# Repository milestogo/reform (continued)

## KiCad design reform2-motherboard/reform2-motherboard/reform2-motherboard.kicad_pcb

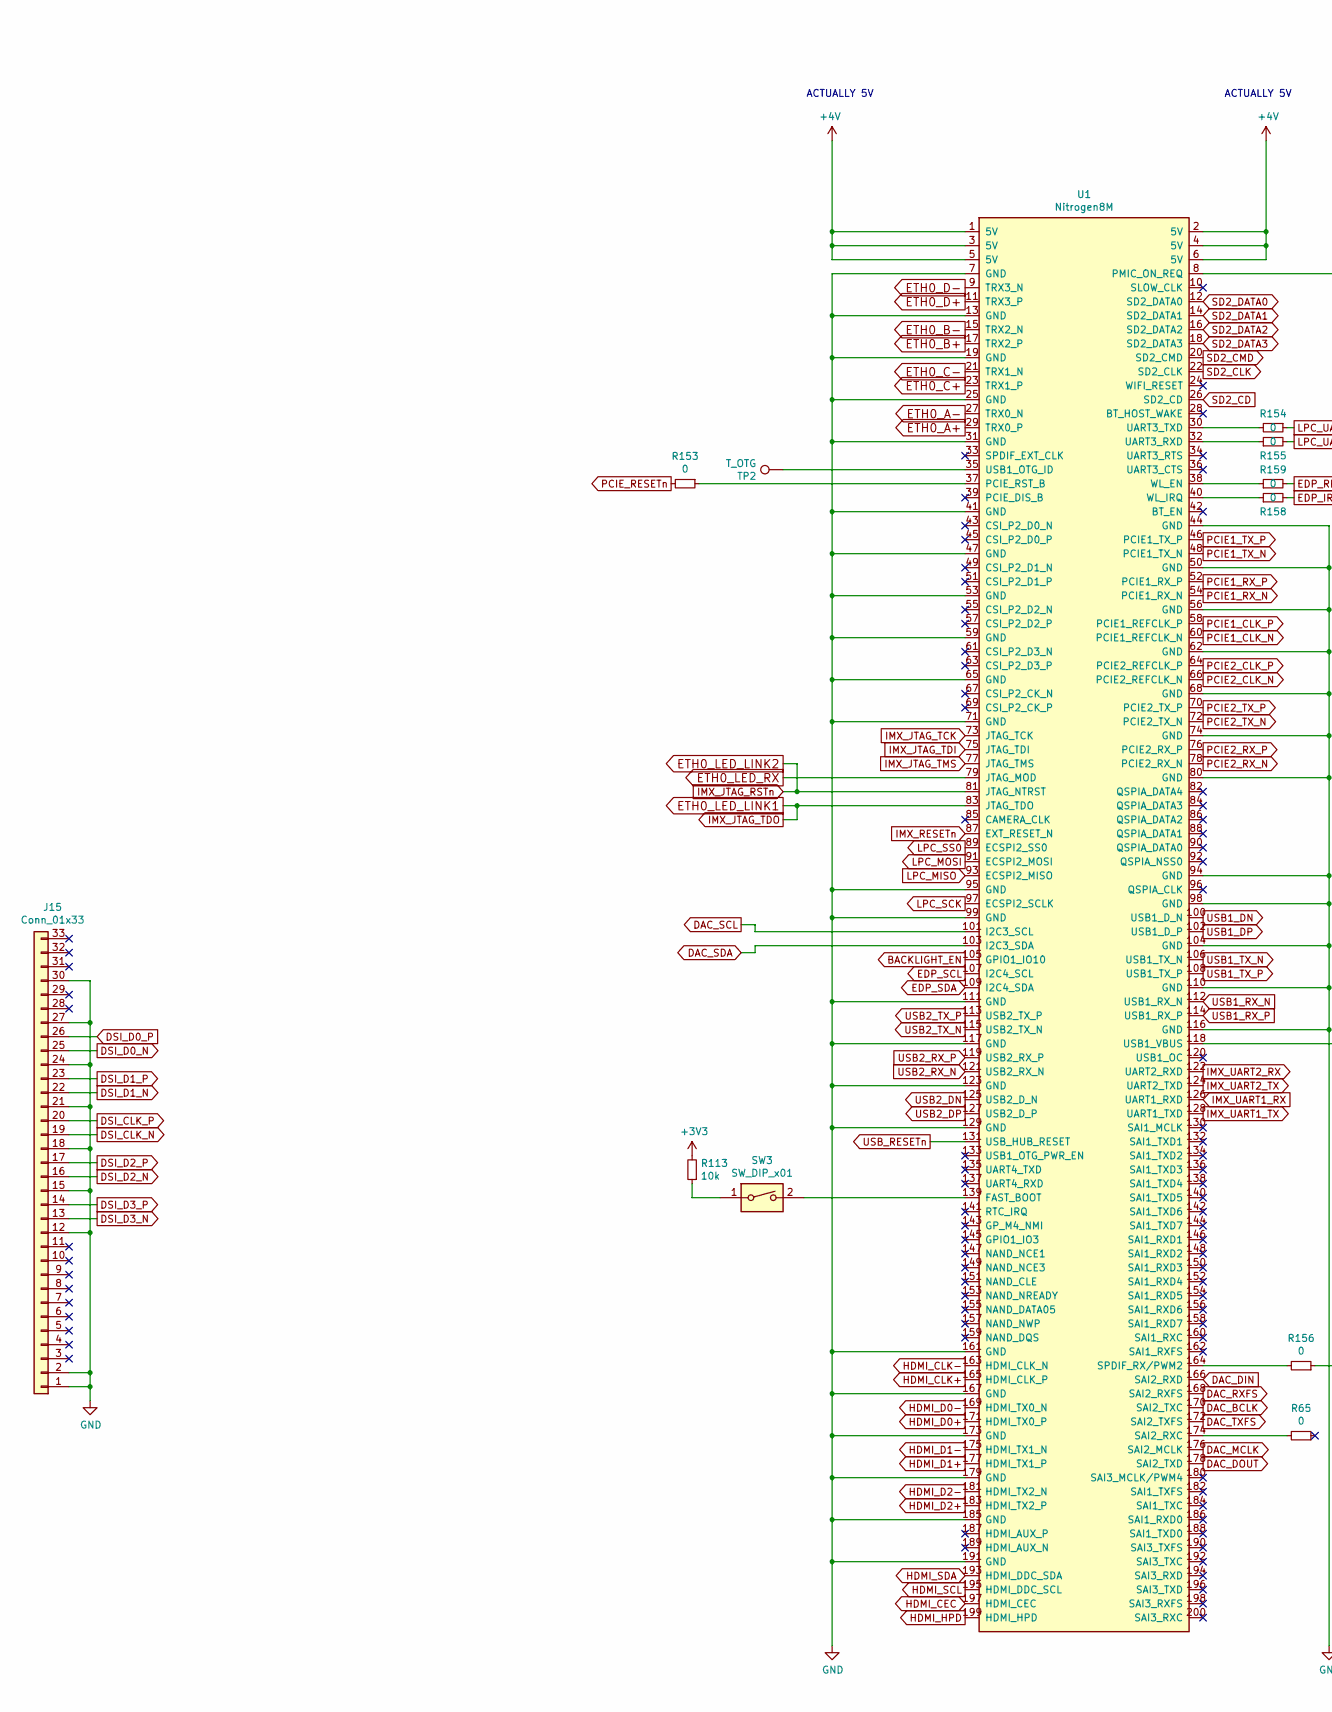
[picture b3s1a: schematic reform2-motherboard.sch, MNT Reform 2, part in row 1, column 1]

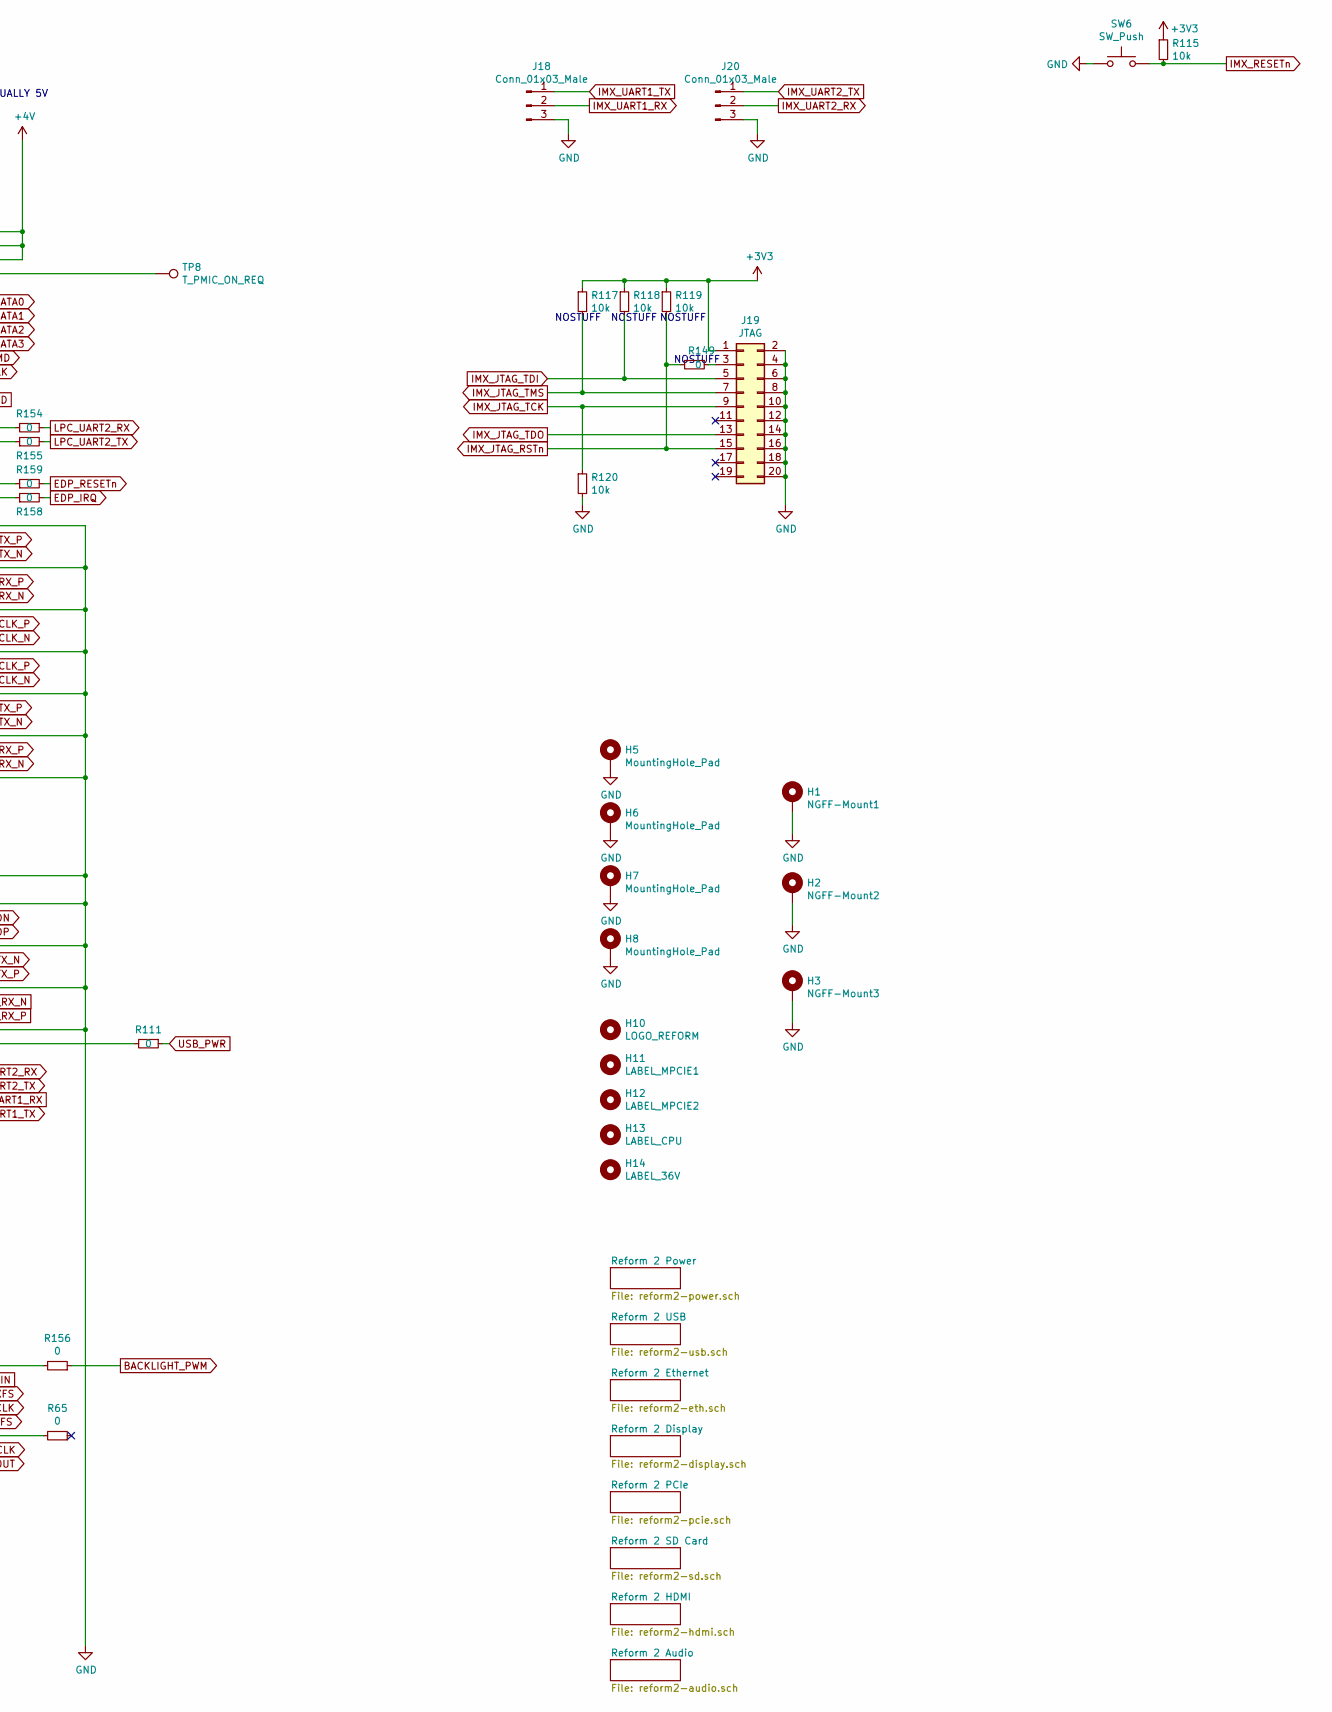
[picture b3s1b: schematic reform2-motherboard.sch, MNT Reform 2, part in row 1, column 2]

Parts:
H1: NGFF-Mount1; MountingHole_3.2mm_M3_DIN965_Pad
H2: NGFF-Mount2; MountingHole_3.2mm_M3_DIN965_Pad
H3: NGFF-Mount3; MountingHole_3.2mm_M3_DIN965_Pad
H5, H6, H7, H8: MountingHole_Pad; MountingHole_2.2mm_M2_DIN965_Pad
H10: LOGO_REFORM; mntreform
H11: LABEL_MPCIE1; mpcie
H12: LABEL_MPCIE2; nvme
H13: LABEL_CPU; cpu
H14: LABEL_36V; 36v
J15: Conn_01x33; Hirose_FH12-33S-0.5SH_1x33-1MP_P0.50mm_Horizontal
J18, J20: Conn_01x03_Male; PinHeader_1x03_P2.54mm_Vertical
J19: JTAG; PinHeader_2x10_P2.54mm_Vertical
R65, R111, R149, R153, R154, R155, R156, R158, R159: 0; R_0603_1608Metric
R113, R115, R117, R118, R119, R120: 10k; R_0603_1608Metric
SW3: SW_DIP_x01; SW_DIP_SPSTx01_Slide_Omron_A6S-110x_W8.9mm_P2.54mm
SW6: SW_Push; SW_Push_1P1T_NO_CK_KMR2
TP2: T_OTG; TestPoint_Pad_D1.0mm
TP8: T_PMIC_ON_REQ; TestPoint_Pad_D1.0mm
U1: Nitrogen8M; TE_1473149-4

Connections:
+4V: U1.1 (5V), U1.2 (5V), U1.3 (5V), U1.4 (5V), U1.5 (5V), U1.6 (5V); also elsewhere on the board
BACKLIGHT_EN: U1.105 (GPIO1_IO10); also elsewhere on the board
BACKLIGHT_PWM: R156.1; also elsewhere on the board
DAC_BCLK: U1.170 (SAI2_TXC); also elsewhere on the board
DAC_DIN: U1.166 (SAI2_RXD); also elsewhere on the board
DAC_DOUT: U1.178 (SAI2_TXD); also elsewhere on the board
DAC_MCLK: U1.176 (SAI2_MCLK); also elsewhere on the board
DAC_RXFS: U1.168 (SAI2_RXFS); also elsewhere on the board
DAC_SCL: U1.101 (I2C3_SCL); also elsewhere on the board
DAC_SDA: U1.103 (I2C3_SDA); also elsewhere on the board
DAC_TXFS: U1.172 (SAI2_TXFS); also elsewhere on the board
DSI_CLK_N: J15.19; also elsewhere on the board
DSI_CLK_P: J15.20; also elsewhere on the board
DSI_D0_N: J15.25; also elsewhere on the board
DSI_D0_P: J15.26; also elsewhere on the board
DSI_D1_N: J15.22; also elsewhere on the board
DSI_D1_P: J15.23; also elsewhere on the board
DSI_D2_N: J15.16; also elsewhere on the board
DSI_D2_P: J15.17; also elsewhere on the board
DSI_D3_N: J15.13; also elsewhere on the board
DSI_D3_P: J15.14; also elsewhere on the board
EDP_IRQ: R158.2; also elsewhere on the board
EDP_RESETn: R159.2; also elsewhere on the board
EDP_SCL: U1.107 (I2C4_SCL); also elsewhere on the board
EDP_SDA: U1.109 (I2C4_SDA); also elsewhere on the board
ETH0_A+: U1.29 (TRX0_P); also elsewhere on the board
ETH0_A-: U1.27 (TRX0_N); also elsewhere on the board
ETH0_B+: U1.17 (TRX2_P); also elsewhere on the board
ETH0_B-: U1.15 (TRX2_N); also elsewhere on the board
ETH0_C+: U1.23 (TRX1_P); also elsewhere on the board
ETH0_C-: U1.21 (TRX1_N); also elsewhere on the board
ETH0_D+: U1.11 (TRX3_P); also elsewhere on the board
ETH0_D-: U1.9 (TRX3_N); also elsewhere on the board
ETH0_LED_LINK1: J19.13, U1.83 (JTAG_TDO); also elsewhere on the board
ETH0_LED_LINK2: J19.15, R119.2, R149.2, U1.81 (JTAG_NTRST); also elsewhere on the board
ETH0_LED_RX: U1.79 (JTAG_MOD); also elsewhere on the board
GND: H1.1, H2.1, H3.1, H5.1, H6.1, H7.1, H8.1, J15.1, J15.2, J15.12, J15.15, J15.18, J15.21, J15.24, J15.27, J15.30, J18.3, J19.2, J19.4, J19.6, J19.8, J19.10, J19.12, J19.14, J19.16, J19.18, J19.20, J20.3, R120.2, SW6.1, U1.7 (GND), U1.13 (GND), U1.19 (GND), U1.25 (GND), U1.31 (GND), U1.41 (GND), U1.44 (GND), U1.47 (GND), U1.50 (GND), U1.53 (GND), U1.56 (GND), U1.59 (GND), U1.62 (GND), U1.65 (GND), U1.68 (GND), U1.71 (GND), U1.74 (GND), U1.80 (GND), U1.94 (GND), U1.95 (GND), U1.98 (GND), U1.99 (GND), U1.104 (GND), U1.110 (GND), U1.111 (GND), U1.116 (GND), U1.117 (GND), U1.123 (GND), U1.129 (GND), U1.161 (GND), U1.167 (GND), U1.173 (GND), U1.179 (GND), U1.185 (GND), U1.191 (GND); also elsewhere on the board
HDMI_CEC: U1.197 (HDMI_CEC); also elsewhere on the board
HDMI_CLK+: U1.165 (HDMI_CLK_P); also elsewhere on the board
HDMI_CLK-: U1.163 (HDMI_CLK_N); also elsewhere on the board
HDMI_D0+: U1.171 (HDMI_TX0_P); also elsewhere on the board
HDMI_D0-: U1.169 (HDMI_TX0_N); also elsewhere on the board
HDMI_D1+: U1.177 (HDMI_TX1_P); also elsewhere on the board
HDMI_D1-: U1.175 (HDMI_TX1_N); also elsewhere on the board
HDMI_D2+: U1.183 (HDMI_TX2_P); also elsewhere on the board
HDMI_D2-: U1.181 (HDMI_TX2_N); also elsewhere on the board
HDMI_HPD: U1.199 (HDMI_HPD); also elsewhere on the board
HDMI_SCL: U1.195 (HDMI_DDC_SCL); also elsewhere on the board
HDMI_SDA: U1.193 (HDMI_DDC_SDA); also elsewhere on the board
IMX_JTAG_TCK: J19.9, R120.1, U1.73 (JTAG_TCK); also elsewhere on the board
IMX_JTAG_TDI: J19.5, R118.2, U1.75 (JTAG_TDI); also elsewhere on the board
IMX_JTAG_TMS: J19.7, R117.2, U1.77 (JTAG_TMS); also elsewhere on the board
IMX_RESETn: R115.2, SW6.2, U1.87 (EXT_RESET_N); also elsewhere on the board
IMX_UART1_RX: J18.2, U1.126 (UART1_RXD); also elsewhere on the board
IMX_UART1_TX: J18.1, U1.128 (UART1_TXD); also elsewhere on the board
IMX_UART2_RX: J20.2, U1.122 (UART2_RXD); also elsewhere on the board
IMX_UART2_TX: J20.1, U1.124 (UART2_TXD); also elsewhere on the board
LPC_MISO: U1.93 (ECSPI2_MISO); also elsewhere on the board
LPC_MOSI: U1.91 (ECSPI2_MOSI); also elsewhere on the board
LPC_SCK: U1.97 (ECSPI2_SCLK); also elsewhere on the board
LPC_SS0: U1.89 (ECSPI2_SS0); also elsewhere on the board
LPC_UART2_RX: R154.1; also elsewhere on the board
LPC_UART2_TX: R155.2; also elsewhere on the board
unnamed: J19.3, R149.1
unnamed 349: R65.2, U1.174 (SAI2_RXC); also elsewhere on the board
unnamed 368: R111.2, U1.118 (USB1_VBUS); also elsewhere on the board
unnamed: R113.1, SW3.1
unnamed 384: R153.1, U1.37 (PCIE_RST_B); also elsewhere on the board
unnamed 385: R154.2, U1.30 (UART3_TXD); also elsewhere on the board
unnamed 386: R155.1, U1.32 (UART3_RXD); also elsewhere on the board
unnamed 387: R156.2, U1.164 (SPDIF_RX/PWM2); also elsewhere on the board
unnamed 388: R158.1, U1.40 (WL_IRQ); also elsewhere on the board
unnamed 389: R159.1, U1.38 (WL_EN); also elsewhere on the board
unnamed 390: SW3.2, U1.139 (FAST_BOOT); also elsewhere on the board
unnamed 392: TP2.1, U1.35 (USB1_OTG_ID); also elsewhere on the board
unnamed 397: TP8.1, U1.8 (PMIC_ON_REQ); also elsewhere on the board
unnamed 399: U1.10 (SLOW_CLK); also elsewhere on the board
unnamed 400: U1.24 (WIFI_RESET); also elsewhere on the board
unnamed 401: U1.28 (BT_HOST_WAKE); also elsewhere on the board
unnamed 402: U1.33 (SPDIF_EXT_CLK); also elsewhere on the board
unnamed 403: U1.34 (UART3_RTS); also elsewhere on the board
unnamed 404: U1.36 (UART3_CTS); also elsewhere on the board
unnamed 405: U1.39 (PCIE_DIS_B); also elsewhere on the board
unnamed 406: U1.42 (BT_EN); also elsewhere on the board
unnamed 407: U1.43 (CSI_P2_D0_N); also elsewhere on the board
unnamed 408: U1.45 (CSI_P2_D0_P); also elsewhere on the board
unnamed 409: U1.49 (CSI_P2_D1_N); also elsewhere on the board
unnamed 410: U1.51 (CSI_P2_D1_P); also elsewhere on the board
unnamed 411: U1.55 (CSI_P2_D2_N); also elsewhere on the board
unnamed 412: U1.57 (CSI_P2_D2_P); also elsewhere on the board
unnamed 413: U1.61 (CSI_P2_D3_N); also elsewhere on the board
unnamed 414: U1.63 (CSI_P2_D3_P); also elsewhere on the board
unnamed 415: U1.67 (CSI_P2_CK_N); also elsewhere on the board
unnamed 416: U1.69 (CSI_P2_CK_P); also elsewhere on the board
unnamed 417: U1.82 (QSPIA_DATA4); also elsewhere on the board
unnamed 418: U1.84 (QSPIA_DATA3); also elsewhere on the board
unnamed 419: U1.85 (CAMERA_CLK); also elsewhere on the board
unnamed 420: U1.86 (QSPIA_DATA2); also elsewhere on the board
unnamed 421: U1.88 (QSPIA_DATA1); also elsewhere on the board
unnamed 422: U1.90 (QSPIA_DATA0); also elsewhere on the board
unnamed 423: U1.92 (QSPIA_NSS0); also elsewhere on the board
unnamed 424: U1.96 (QSPIA_CLK); also elsewhere on the board
unnamed 425: U1.120 (USB1_OC); also elsewhere on the board
unnamed 426: U1.130 (SAI1_MCLK); also elsewhere on the board
unnamed 427: U1.132 (SAI1_TXD1); also elsewhere on the board
unnamed 428: U1.133 (USB1_OTG_PWR_EN); also elsewhere on the board
unnamed 429: U1.134 (SAI1_TXD2); also elsewhere on the board
unnamed 430: U1.135 (UART4_TXD); also elsewhere on the board
unnamed 431: U1.136 (SAI1_TXD3); also elsewhere on the board
unnamed 432: U1.137 (UART4_RXD); also elsewhere on the board
unnamed 433: U1.138 (SAI1_TXD4); also elsewhere on the board
unnamed 434: U1.140 (SAI1_TXD5); also elsewhere on the board
unnamed 435: U1.141 (RTC_IRQ); also elsewhere on the board
unnamed 436: U1.142 (SAI1_TXD6); also elsewhere on the board
unnamed 437: U1.143 (GP_M4_NMI); also elsewhere on the board
unnamed 438: U1.144 (SAI1_TXD7); also elsewhere on the board
unnamed 439: U1.145 (GPIO1_IO3); also elsewhere on the board
unnamed 440: U1.146 (SAI1_RXD1); also elsewhere on the board
unnamed 441: U1.147 (NAND_NCE1); also elsewhere on the board
unnamed 442: U1.148 (SAI1_RXD2); also elsewhere on the board
unnamed 443: U1.149 (NAND_NCE3); also elsewhere on the board
unnamed 444: U1.150 (SAI1_RXD3); also elsewhere on the board
unnamed 445: U1.151 (NAND_CLE); also elsewhere on the board
unnamed 446: U1.152 (SAI1_RXD4); also elsewhere on the board
unnamed 447: U1.153 (NAND_NREADY); also elsewhere on the board
unnamed 448: U1.154 (SAI1_RXD5); also elsewhere on the board
unnamed 449: U1.155 (NAND_DATA05); also elsewhere on the board
unnamed 450: U1.156 (SAI1_RXD6); also elsewhere on the board
unnamed 451: U1.157 (NAND_NWP); also elsewhere on the board
unnamed 452: U1.158 (SAI1_RXD7); also elsewhere on the board
unnamed 453: U1.159 (NAND_DQS); also elsewhere on the board
unnamed 454: U1.160 (SAI1_RXC); also elsewhere on the board
unnamed 455: U1.162 (SAI1_RXFS); also elsewhere on the board
unnamed 456: U1.180 (SAI3_MCLK/PWM4); also elsewhere on the board
unnamed 457: U1.182 (SAI1_TXFS); also elsewhere on the board
unnamed 458: U1.184 (SAI1_TXC); also elsewhere on the board
unnamed 459: U1.186 (SAI1_RXD0); also elsewhere on the board
unnamed 460: U1.187 (HDMI_AUX_P); also elsewhere on the board
unnamed 461: U1.188 (SAI1_TXD0); also elsewhere on the board
unnamed 462: U1.189 (HDMI_AUX_N); also elsewhere on the board
unnamed 463: U1.190 (SAI3_TXFS); also elsewhere on the board
unnamed 464: U1.192 (SAI3_TXC); also elsewhere on the board
unnamed 465: U1.194 (SAI3_RXD); also elsewhere on the board
unnamed 466: U1.196 (SAI3_TXD); also elsewhere on the board
unnamed 467: U1.198 (SAI3_RXFS); also elsewhere on the board
unnamed 468: U1.200 (SAI3_RXC); also elsewhere on the board
PCIE1_CLK_N: U1.60 (PCIE1_REFCLK_N); also elsewhere on the board
PCIE1_CLK_P: U1.58 (PCIE1_REFCLK_P); also elsewhere on the board
PCIE1_RX_N: U1.54 (PCIE1_RX_N); also elsewhere on the board
PCIE1_RX_P: U1.52 (PCIE1_RX_P); also elsewhere on the board
PCIE1_TX_N: U1.48 (PCIE1_TX_N); also elsewhere on the board
PCIE1_TX_P: U1.46 (PCIE1_TX_P); also elsewhere on the board
PCIE2_CLK_N: U1.66 (PCIE2_REFCLK_N); also elsewhere on the board
PCIE2_CLK_P: U1.64 (PCIE2_REFCLK_P); also elsewhere on the board
PCIE2_RX_N: U1.78 (PCIE2_RX_N); also elsewhere on the board
PCIE2_RX_P: U1.76 (PCIE2_RX_P); also elsewhere on the board
PCIE2_TX_N: U1.72 (PCIE2_TX_N); also elsewhere on the board
PCIE2_TX_P: U1.70 (PCIE2_TX_P); also elsewhere on the board
PCIE_RESETn: R153.2; also elsewhere on the board
SD2_CD: U1.26 (SD2_CD); also elsewhere on the board
SD2_CLK: U1.22 (SD2_CLK); also elsewhere on the board
SD2_CMD: U1.20 (SD2_CMD); also elsewhere on the board
SD2_DATA0: U1.12 (SD2_DATA0); also elsewhere on the board
SD2_DATA1: U1.14 (SD2_DATA1); also elsewhere on the board
SD2_DATA2: U1.16 (SD2_DATA2); also elsewhere on the board
SD2_DATA3: U1.18 (SD2_DATA3); also elsewhere on the board
USB1_DN: U1.100 (USB1_D_N); also elsewhere on the board
USB1_DP: U1.102 (USB1_D_P); also elsewhere on the board
USB1_RX_N: U1.112 (USB1_RX_N); also elsewhere on the board
USB1_RX_P: U1.114 (USB1_RX_P); also elsewhere on the board
USB1_TX_N: U1.106 (USB1_TX_N); also elsewhere on the board
USB1_TX_P: U1.108 (USB1_TX_P); also elsewhere on the board
USB2_DN: U1.125 (USB2_D_N); also elsewhere on the board
USB2_DP: U1.127 (USB2_D_P); also elsewhere on the board
USB2_RX_N: U1.121 (USB2_RX_N); also elsewhere on the board
USB2_RX_P: U1.119 (USB2_RX_P); also elsewhere on the board
USB2_TX_N: U1.115 (USB2_TX_N); also elsewhere on the board
USB2_TX_P: U1.113 (USB2_TX_P); also elsewhere on the board
USB_PWR: R111.1; also elsewhere on the board
USB_RESETn: U1.131 (USB_HUB_RESET); also elsewhere on the board

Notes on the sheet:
ACTUALLY 5V
NOSTUFF

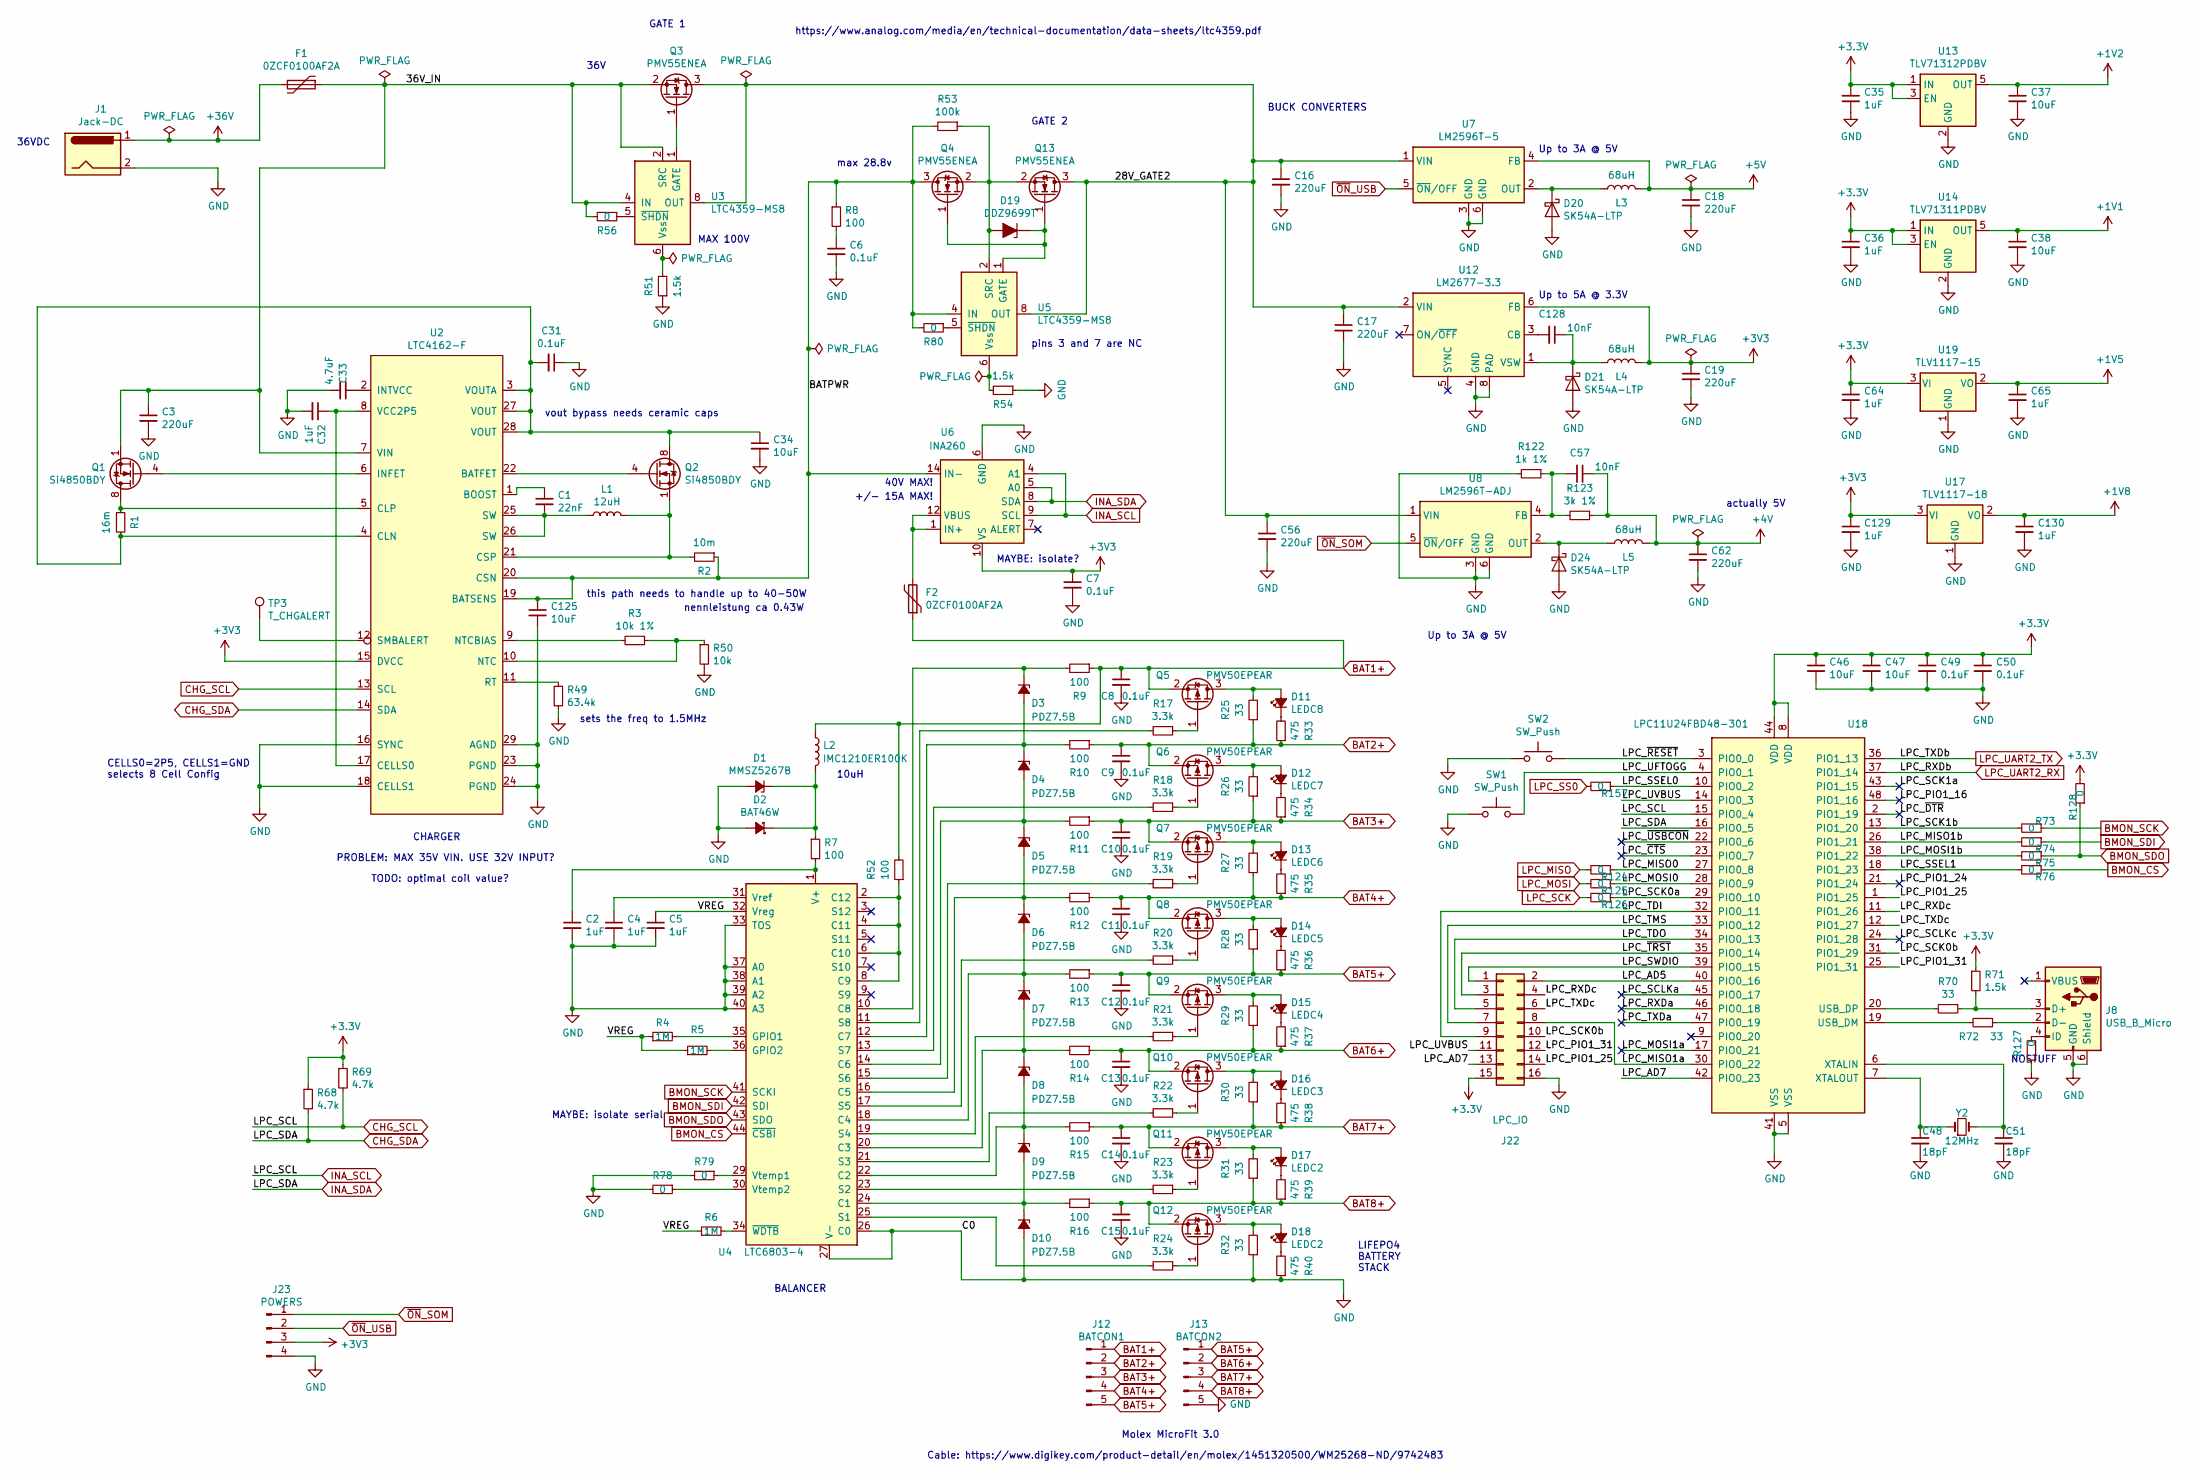
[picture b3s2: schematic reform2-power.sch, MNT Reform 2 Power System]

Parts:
C1: 22nF; C_0603_1608Metric
C2, C4, C5, C32, C35, C36, C64, C65, C129, C130: 1uF; C_0603_1608Metric
C3, C16, C17, C18, C19, C56, C62: 220uF; CP_Elec_8x10
C6, C7, C8, C9, C10, C11, C12, C13, C14, C15, C31, C49, C50: 0.1uF; C_0603_1608Metric
C33: 4.7uF; C_0603_1608Metric
C34, C37, C38, C46, C47, C125: 10uF; C_0603_1608Metric
C48, C51: 18pF; C_0603_1608Metric
C57, C128: 10nF; C_0603_1608Metric
D1: MMSZ5267B; D_SOD-123
D2: BAT46W; D_SOD-123
D3, D4, D5, D6, D7, D8, D9, D10: PDZ7.5B; D_SOD-323
D11: LEDC8; LED_0603_1608Metric
D12: LEDC7; LED_0603_1608Metric
D13: LEDC6; LED_0603_1608Metric
D14: LEDC5; LED_0603_1608Metric
D15: LEDC4; LED_0603_1608Metric
D16: LEDC3; LED_0603_1608Metric
D17, D18: LEDC2; LED_0603_1608Metric
D19: DDZ9699T; D_SOD-523
D20, D21, D24: SK54A-LTP; D_SMA
F1, F2: 0ZCF0100AF2A; Fuse_2920_7451Metric
J1: Jack-DC; SWC_RAPC712X
J8: USB_B_Micro; USB_Micro-B_Molex-105017-0001
J12: BATCON1; Molex_Micro-Fit_3.0_43650-0500_1x05_P3.00mm_Horizontal
J13: BATCON2; Molex_Micro-Fit_3.0_43650-0500_1x05_P3.00mm_Horizontal
J22: LPC_IO; PinHeader_2x08_P2.54mm_Vertical
J23: POWERS; PinHeader_1x04_P2.54mm_Vertical
L1: 12uH; L_Bourns_SRR1260
L2: IMC1210ER100K; L_1210_3225Metric
L3, L4, L5: 68uH; L_Bourns_SRR1210A
Q1, Q2: Si4850BDY; SOIC-8_3.9x4.9mm_P1.27mm
Q3, Q4, Q13: PMV55ENEA; SOT-23
Q5, Q6, Q7, Q8, Q9, Q10, Q11, Q12: PMV50EPEAR; SOT-23
R1: 16m; R_0612_1632Metric
R2: 10m; R_0612_1632Metric
R3: 10k 1%; R_0603_1608Metric
R4, R5, R6: 1M; R_0603_1608Metric
R7, R8, R9, R10, R11, R12, R13, R14, R15, R16, R52: 100; R_0603_1608Metric
R17, R18, R19, R20, R21, R22, R23, R24: 3.3k; R_0603_1608Metric
R25, R26, R27, R28, R29, R30, R31, R32, R70, R72: 33; R_0603_1608Metric
R33, R34, R35, R36, R37, R38, R39, R40: 475; R_0603_1608Metric
R49: 63.4k; R_0603_1608Metric
R50: 10k; R_0603_1608Metric
R51, R54, R71: 1.5k; R_0603_1608Metric
R53: 100k; R_0603_1608Metric
R56, R73, R74, R75, R76, R78, R79, R80, R124, R125, R126, R127, R128, R157: 0; R_0603_1608Metric
R68, R69: 4.7k; R_0603_1608Metric
R122: 1k 1%; R_0603_1608Metric
R123: 3k 1%; R_0603_1608Metric
SW1, SW2: SW_Push; SW_Push_1P1T_NO_CK_KMR2
TP3: T_CHGALERT; TestPoint_Pad_D1.0mm
U2: LTC4162-F; QFN-28-1EP_4x5mm_P0.5mm_EP2.65x3.65mm
U3, U5: LTC4359-MS8; MSOP-8_3x3mm_P0.65mm
U4: LTC6803-4; SSOP-44_5.3x12.8mm_P0.5mm
U6: INA260; TSSOP-16_4.4x5mm_P0.65mm
U7: LM2596T-5; TO-263-5_TabPin6
U8: LM2596T-ADJ; TO-263-5_TabPin6
U12: LM2677-3.3; TO-263-7_TabPin8
U13: TLV71312PDBV; SOT-23-5
U14: TLV71311PDBV; SOT-23-5
U17: TLV1117-18; SOT-223
U18: LPC11U24FBD48-301; LQFP-48_7x7mm_P0.5mm
U19: TLV1117-15; SOT-223
Y2: 12MHz; Crystal_SMD_Abracon_ABM8G-4Pin_3.2x2.5mm

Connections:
+1V1: C38.1, U14.5 (OUT); also elsewhere on the board
+1V2: C37.1, U13.5 (OUT); also elsewhere on the board
+1V5: C65.1, U19.2 (VO); also elsewhere on the board
+1V8: C130.1, U17.2 (VO); also elsewhere on the board
+4V: C57.1, C62.1, L5.2, R123.1; also elsewhere on the board
+36V: F1.2, J1.1
/Reform 2 Power/28V_GATE2: C16.1, C17.1, C56.1, Q3.3 (D), Q13.3 (D), U3.8 (OUT), U5.8 (OUT), U7.1 (VIN), U8.1 (VIN), U12.2 (VIN)
/Reform 2 Power/36V_IN: C3.1, F1.1, Q1.1 (S), Q1.2 (S), Q1.3 (S), Q3.2 (S), R56.2, U2.7 (VIN), U3.2 (SRC), U3.4 (IN)
/Reform 2 Power/BATPWR: C125.1, Q4.3 (D), R2.1, R8.1, R53.2, R80.2, U2.19 (BATSENS), U2.20 (CSN), U5.4 (IN), U6.14 (IN-), U6.15 (IN-), U6.16 (IN-)
/Reform 2 Power/LPC_AD5: J22.2, U18.40 (PIO0_16)
/Reform 2 Power/LPC_AD7: J22.13, U18.42 (PIO0_23)
/Reform 2 Power/LPC_MISO0: R124.1, U18.27 (PIO0_8)
/Reform 2 Power/LPC_MISO1a: J22.8, U18.30 (PIO0_22)
/Reform 2 Power/LPC_MISO1b: R74.2, U18.26 (PIO1_21)
/Reform 2 Power/LPC_MOSI0: R125.1, U18.28 (PIO0_9)
/Reform 2 Power/LPC_MOSI1a: U18.17 (PIO0_21)
/Reform 2 Power/LPC_MOSI1b: R75.2, U18.38 (PIO1_22)
/Reform 2 Power/LPC_PIO1_16: U18.48 (PIO1_16)
/Reform 2 Power/LPC_PIO1_24: U18.21 (PIO1_24)
/Reform 2 Power/LPC_PIO1_25: J22.14, U18.1 (PIO1_25)
/Reform 2 Power/LPC_PIO1_31: J22.12, U18.25 (PIO1_31)
/Reform 2 Power/LPC_RXDa: U18.46 (PIO0_18)
/Reform 2 Power/LPC_RXDc: J22.4, U18.11 (PIO1_26)
/Reform 2 Power/LPC_SCK0a: R126.1, U18.29 (PIO0_10)
/Reform 2 Power/LPC_SCK0b: J22.10, U18.31 (PIO1_29)
/Reform 2 Power/LPC_SCK1a: U18.43 (PIO1_15)
/Reform 2 Power/LPC_SCK1b: R73.2, U18.13 (PIO1_20)
/Reform 2 Power/LPC_SCLKa: U18.45 (PIO0_17)
/Reform 2 Power/LPC_SCLKc: U18.24 (PIO1_28)
/Reform 2 Power/LPC_SSEL0: R157.1, U18.10 (PIO0_2)
/Reform 2 Power/LPC_SSEL1: R76.2, U18.18 (PIO1_23)
/Reform 2 Power/LPC_SWDIO: J22.1, U18.39 (PIO0_15)
/Reform 2 Power/LPC_TDI: J22.9, U18.32 (PIO0_11)
/Reform 2 Power/LPC_TDO: J22.5, U18.34 (PIO0_13)
/Reform 2 Power/LPC_TMS: J22.7, U18.33 (PIO0_12)
/Reform 2 Power/LPC_TXDa: U18.47 (PIO0_19)
/Reform 2 Power/LPC_TXDc: J22.6, U18.12 (PIO1_27)
/Reform 2 Power/LPC_UFTOGG: SW1.2, U18.4 (PIO0_1)
/Reform 2 Power/LPC_UVBUS: J22.11, U18.14 (PIO0_3)
/Reform 2 Power/LPC_~CTS: U18.23 (PIO0_7)
/Reform 2 Power/LPC_~DTR: U18.2 (PIO1_19)
/Reform 2 Power/LPC_~RESET: SW2.2, U18.3 (PIO0_0)
/Reform 2 Power/LPC_~TRST: J22.3, U18.35 (PIO0_14)
/Reform 2 Power/LPC_~USBCON: U18.22 (PIO0_6)
/Reform 2 Power/VREG: C5.1, R4.1, R5.1, R6.1, U4.32 (Vreg)
BAT1+: C8.1, F2.1, J12.1, L2.1, Q5.2 (S), R9.1, R52.2
BAT2+: C9.1, J12.2, Q6.2 (S), R10.1, R25.1, R33.1
BAT3+: C10.1, J12.3, Q7.2 (S), R11.1, R26.1, R34.1
BAT4+: C11.1, J12.4, Q8.2 (S), R12.1, R27.1, R35.1
BAT5+: C12.1, J12.5, J13.1, Q9.2 (S), R13.1, R28.1, R36.1
BAT6+: C13.1, J13.2, Q10.2 (S), R14.1, R29.1, R37.1
BAT7+: C14.1, J13.3, Q11.2 (S), R15.1, R30.1, R38.1
BAT8+: C15.1, J13.4, Q12.2 (S), R16.1, R31.1, R39.1
BMON_CS: R76.1, U4.44 (~CSBI~)
BMON_SCK: R73.1, U4.41 (SCKI)
BMON_SDI: R74.1, U4.42 (SDI)
BMON_SDO: R75.1, R128.1, U4.43 (SDO)
CHG_SCL: R69.2, U2.13 (SCL), U6.4 (A1), U6.9 (SCL), U18.15 (PIO0_4)
CHG_SDA: R68.2, U2.14 (SDA), U6.5 (A0), U6.8 (SDA), U18.16 (PIO0_5)
GND: C2.2, C3.2, C4.2, C5.2, C6.2, C7.2, C8.2, C9.2, C10.2, C11.2, C12.2, C13.2, C14.2, C15.2, C16.2, C17.2, C18.2, C19.2, C31.1, C32.2, C33.2, C34.2, C35.2, C36.2, C37.2, C38.2, C46.2, C47.2, C48.2, C49.2, C50.2, C51.2, C56.2, C62.2, C64.2, C65.2, C125.2, C129.2, C130.2, D1.2 (A), D2.2 (A), D10.2 (A), D20.2 (A), D21.2 (A), D24.2 (A), J1.2, J8.5 (GND), J8.6 (Shield), J13.5, J22.16, J23.4, R32.1, R40.1, R49.2, R50.2, R51.1, R54.1, R78.2, R79.2, R122.2, R127.1, SW1.1, SW2.1, U2.16 (SYNC), U2.18 (CELLS1), U2.23 (PGND), U2.24 (PGND), U2.29 (AGND), U4.26 (C0), U4.27 (V-), U4.33 (TOS), U4.37 (A0), U4.38 (A1), U4.39 (A2), U4.40 (A3), U6.6 (GND), U6.11 (GND), U7.3 (GND), U7.6 (GND), U8.3 (GND), U8.6 (GND), U12.4 (GND), U12.8 (PAD), U13.2 (GND), U14.2 (GND), U17.1 (GND), U18.5 (VSS), U18.41 (VSS), U19.1 (GND); also elsewhere on the board
LPC_MISO: R124.2; also elsewhere on the board
LPC_MOSI: R125.2; also elsewhere on the board
LPC_SCK: R126.2; also elsewhere on the board
LPC_SS0: R157.2; also elsewhere on the board
LPC_UART2_RX: U18.37 (PIO1_14); also elsewhere on the board
LPC_UART2_TX: U18.36 (PIO1_13); also elsewhere on the board
unnamed: C1.1, U2.1 (BOOST)
unnamed: C1.2, L1.1, U2.25 (SW), U2.26 (SW)
unnamed: C2.1, R7.2, U4.1 (V+)
unnamed: C4.1, U4.31 (Vref)
unnamed: C6.1, R8.2
unnamed: C31.2, C34.1, Q2.5 (D), Q2.6 (D), Q2.7 (D), Q2.8 (D), R1.2, U2.3 (VOUTA), U2.4 (CLN), U2.27 (VOUT), U2.28 (VOUT)
unnamed: C32.1, U2.8 (VCC2P5), U2.17 (CELLS0)
unnamed: C33.1, U2.2 (INTVCC)
unnamed: C48.1, U18.7 (XTALOUT), Y2.1
unnamed: C51.1, U18.6 (XTALIN), Y2.2
unnamed: C57.2, R122.1, R123.2, U8.4 (FB)
unnamed: C128.1, D21.1 (K), L4.1, U12.1 (VSW)
unnamed: C128.2, U12.3 (CB)
unnamed: D1.1 (K), D2.1 (K), L2.2, R7.1
unnamed: D3.1 (K), R9.2, U4.10 (C8)
unnamed: D3.2 (A), D4.1 (K), R10.2, U4.12 (C7)
unnamed: D4.2 (A), D5.1 (K), R11.2, U4.14 (C6)
unnamed: D5.2 (A), D6.1 (K), R12.2, U4.16 (C5)
unnamed: D6.2 (A), D7.1 (K), R13.2, U4.18 (C4)
unnamed: D7.2 (A), D8.1 (K), R14.2, U4.20 (C3)
unnamed: D8.2 (A), D9.1 (K), R15.2, U4.22 (C2)
unnamed: D9.2 (A), D10.1 (K), R16.2, U4.24 (C1)
unnamed: D11.1 (K), R33.2
unnamed: D11.2 (A), Q5.3 (D), R25.2
unnamed: D12.1 (K), R34.2
unnamed: D12.2 (A), Q6.3 (D), R26.2
unnamed: D13.1 (K), R35.2
unnamed: D13.2 (A), Q7.3 (D), R27.2
unnamed: D14.1 (K), R36.2
unnamed: D14.2 (A), Q8.3 (D), R28.2
unnamed: D15.1 (K), R37.2
unnamed: D15.2 (A), Q9.3 (D), R29.2
unnamed: D16.1 (K), R38.2
unnamed: D16.2 (A), Q10.3 (D), R30.2
unnamed: D17.1 (K), R39.2
unnamed: D17.2 (A), Q11.3 (D), R31.2
unnamed: D18.1 (K), R40.2
unnamed: D18.2 (A), Q12.3 (D), R32.2
unnamed: D19.1 (K), Q4.1 (G), Q13.1 (G), U5.1 (GATE)
unnamed: D19.2 (A), Q4.2 (S), Q13.2 (S), R53.1, U5.2 (SRC)
unnamed: D20.1 (K), L3.1, U7.2 (OUT)
unnamed: D24.1 (K), L5.1, U8.2 (OUT)
unnamed: F2.2, U6.1 (IN+), U6.2 (IN+), U6.3 (IN+), U6.12 (VBUS)
unnamed: J8.2 (D-), R72.1
unnamed: J8.3 (D+), R70.1, R71.2
unnamed: J8.4 (ID), R127.2
unnamed: L1.2, Q2.1 (S), Q2.2 (S), Q2.3 (S), R2.2, U2.21 (CSP)
unnamed: Q1.4 (G), U2.6 (INFET)
unnamed: Q1.5 (D), Q1.6 (D), Q1.7 (D), Q1.8 (D), R1.1, U2.5 (CLP)
unnamed: Q2.4 (G), U2.22 (BATFET)
unnamed: Q3.1 (G), U3.1 (GATE)
unnamed: Q5.1 (G), R17.1
unnamed: Q6.1 (G), R18.1
unnamed: Q7.1 (G), R19.1
unnamed: Q8.1 (G), R20.1
unnamed: Q9.1 (G), R21.1
unnamed: Q10.1 (G), R22.1
unnamed: Q11.1 (G), R23.1
unnamed: Q12.1 (G), R24.1
unnamed: R3.1, R50.1, U2.10 (NTC)
unnamed: R3.2, U2.9 (NTCBIAS)
unnamed: R4.2, U4.35 (GPIO1)
unnamed: R5.2, U4.36 (GPIO2)
unnamed: R6.2, U4.34 (~WDTB~)
unnamed: R17.2, U4.11 (S8)
unnamed: R18.2, U4.13 (S7)
unnamed: R19.2, U4.15 (S6)
unnamed: R20.2, U4.17 (S5)
unnamed: R21.2, U4.19 (S4)
unnamed: R22.2, U4.21 (S3)
unnamed: R23.2, U4.23 (S2)
unnamed: R24.2, U4.25 (S1)
unnamed: R49.1, U2.11 (RT)
unnamed: R51.2, U3.6 (Vss)
unnamed: R52.1, U4.2 (C12), U4.4 (C11), U4.6 (C10), U4.8 (C9)
unnamed: R54.2, U5.6 (Vss)
unnamed: R56.1, U3.5 (~SHDN)
unnamed: R70.2, U18.20 (USB_DP)
unnamed: R72.2, U18.19 (USB_DM)
unnamed: R78.1, U4.30 (Vtemp2)
unnamed: R79.1, U4.29 (Vtemp1)
unnamed: R80.1, U5.5 (~SHDN)
unnamed: TP3.1, U2.12 (SMBALERT)
USB_PWR: C18.1, L3.2, U7.4 (FB); also elsewhere on the board
~ON~_SOM: J23.1, U8.5 (~ON~/OFF)
~ON~_USB: J23.2, U7.5 (~ON~/OFF)

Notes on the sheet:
max 28.8v
BUCK CONVERTERS
MAYBE: isolate serial
MAYBE: isolate?
36VDC
36V
CHARGER
BALANCER
GATE 2
LIFEPO4 BATTERY STACK
TODO: optimal coil value?
https://www.analog.com/media/en/technical-documentation/data-sheets/ltc4359.pdf
CELLS0=2P5, CELLS1=GND selects 8 Cell Config
this path needs to handle up to 40-50W
nennleistung ca 0.43W
GATE 1
10uH
Molex MicroFit 3.0
Cable: https://www.digikey.com/product-detail/en/molex/1451320500/WM25268-ND/9742483
sets the freq to 1.5MHz
vout bypass needs ceramic caps
40V MAX!
+/- 15A MAX!
NOSTUFF
Up to 5A @ 3.3V
Up to 3A @ 5V
pins 3 and 7 are NC
actually 5V
PROBLEM: MAX 35V VIN. USE 32V INPUT?
MAX 100V
